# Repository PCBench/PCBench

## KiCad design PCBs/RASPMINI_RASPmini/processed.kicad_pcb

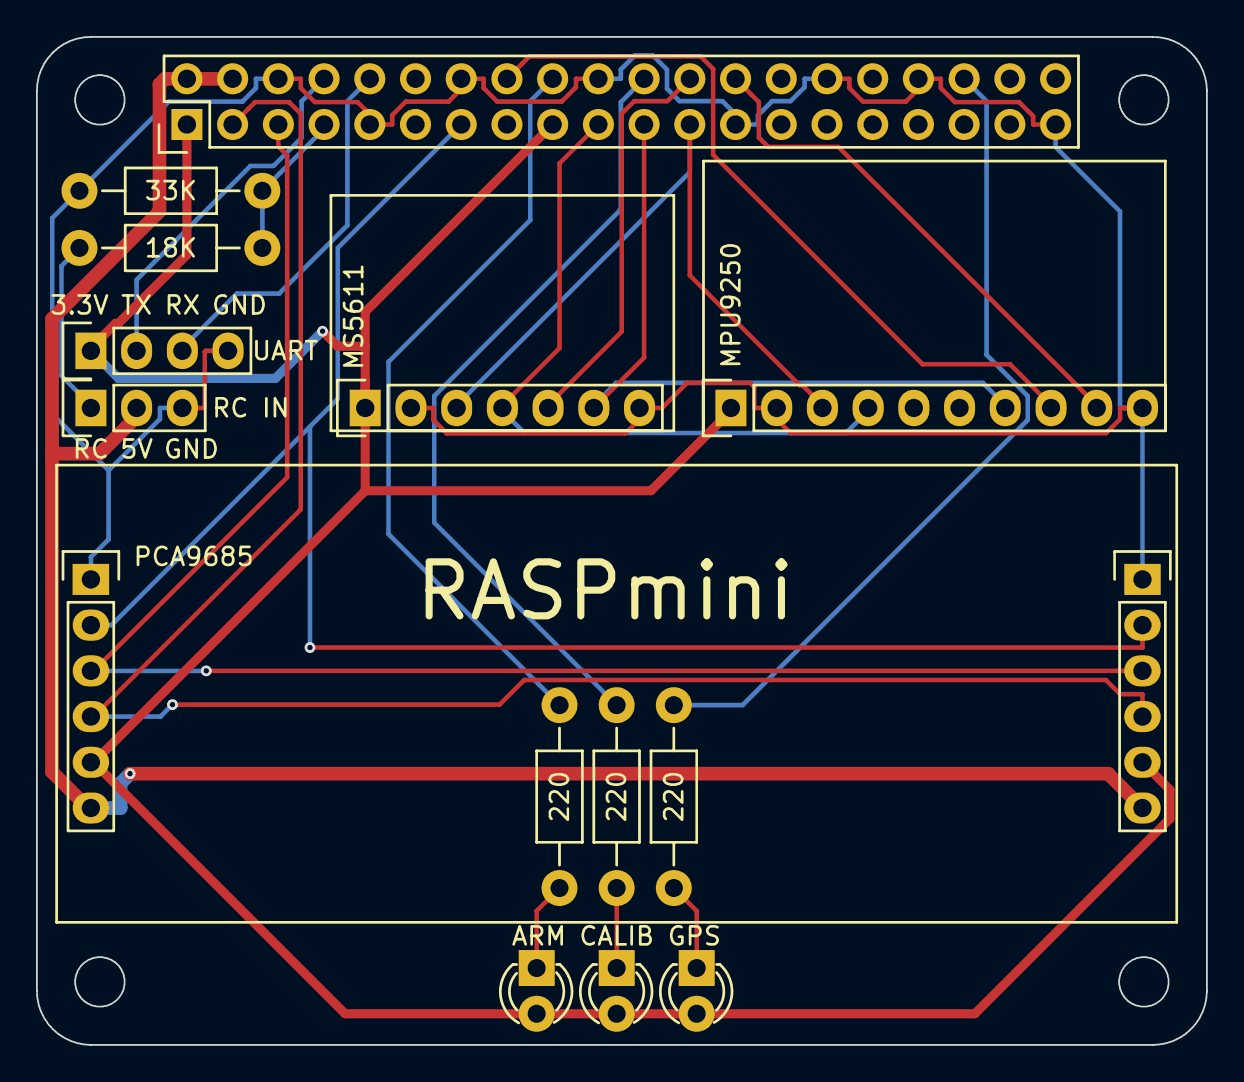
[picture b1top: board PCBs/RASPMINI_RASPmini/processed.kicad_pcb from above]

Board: 2 copper layers, 65.0 x 56.0 mm, 14 parts (0 on the bottom side), 22 nets.

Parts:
D1: ARM; LED-3MM
D2: CALIB; LED-3MM
D3: GPS; LED-3MM
P0: Raspberry PI GPIO; Pin_Header_Straight_2x20
P1: MPU9250
P2: MS5611
P3: PCA9685
P5: UART; Pin_Header_Straight_1x04
P6: RC IN; Pin_Header_Straight_1x03
R1: 18K; Resistor_Horizontal_RM10mm
R2: 33K; Resistor_Horizontal_RM10mm
R3, R4, R5: 220; Resistor_Horizontal_RM10mm

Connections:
+3V3: D1.2, D2.2, D3.2, P0.1, P0.17, P1.1, P2.1, P3.5, P5.1
+5V: P0.2, P0.4, P3.6, P6.2
/CS_BARO: P0.24, P2.5
/CS_MPU: P0.26, P1.9
/EN_PWM: P0.13, P3.2
/LED_ARM: P0.18, R3.2
/LED_CALIBRATION: P0.22, R4.2
/LED_GPS: P0.36, R5.2
/MISO: P0.21, P1.7, P2.6
/MOSI: P0.19, P1.4, P2.4
/MPU_DRDY: P0.16, P1.8
/RC_INPUT: P0.7, R1.2, R2.1
/RXD: P0.10, P5.3
/SCL: P0.5, P3.3
/SCLK: P0.23, P1.3, P2.3
/SDA: P0.3, P3.4
/TXD: P0.8, P5.2
GND: P0.6, P0.9, P0.14, P0.20, P0.25, P0.30, P0.34, P0.39, P1.2, P1.10, P2.2, P2.7, P3.1, P5.4, P6.3, R2.2
unnamed: D1.1, R3.1
unnamed: D2.1, R4.1
unnamed: D3.1, R5.1
unnamed: P6.1, R1.1

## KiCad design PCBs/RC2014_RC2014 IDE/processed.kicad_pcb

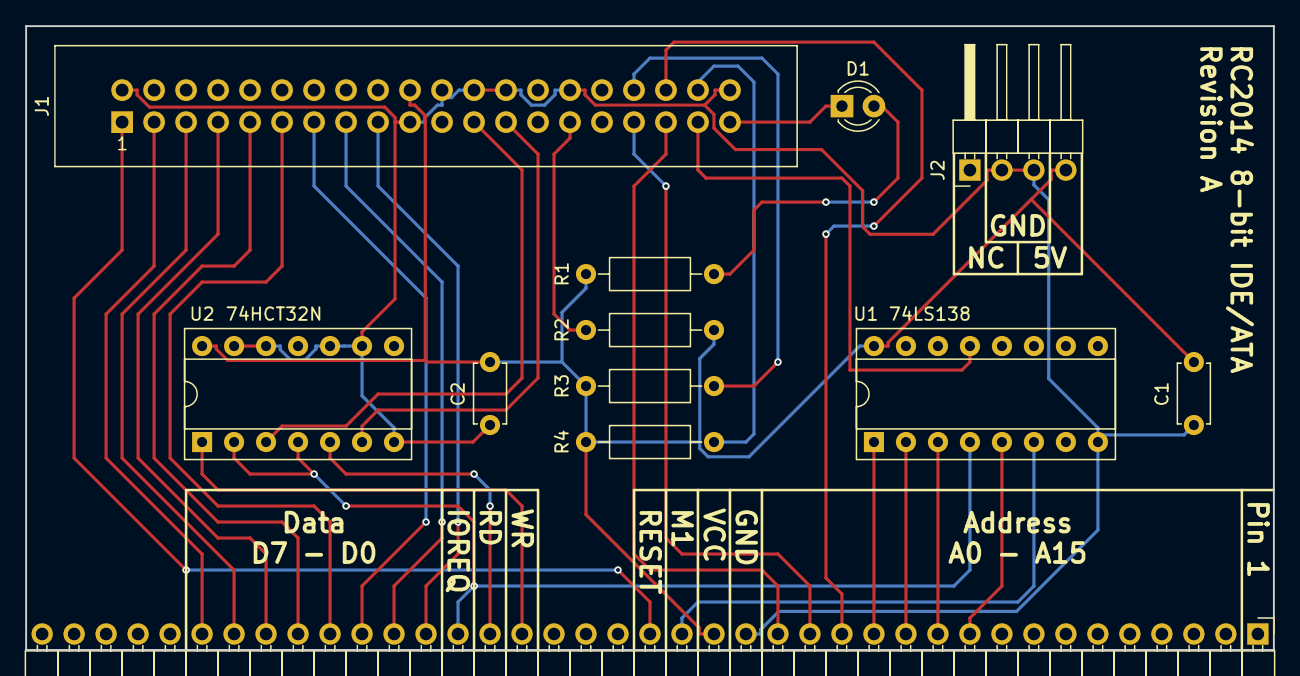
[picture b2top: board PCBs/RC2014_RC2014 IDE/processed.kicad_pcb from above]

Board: 2 copper layers, 99.1 x 49.5 mm, 12 parts (0 on the bottom side), 30 nets.

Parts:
C1, C2: 100nF; C_Disc_D4.7mm_W2.5mm_P5.00mm
D1: LED; LED_D3.0mm
J1: CONN_02X20; IDC_Header_Straight_40pins
J2: Device power; Pin_Header_Angled_1x04_Pitch2.54mm
J4: CONN_01X39; Pin_Header_Angled_1x39_Pitch2.54mm
R1: 330; R_Axial_DIN0207_L6.3mm_D2.5mm_P10.16mm_Horizontal
R2, R3, R4: 1k; R_Axial_DIN0207_L6.3mm_D2.5mm_P10.16mm_Horizontal
U1: 74LS138; DIP-16_W7.62mm_Socket
U2: 74HCT32N; DIP-14_W7.62mm_Socket

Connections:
/IORD: J1.25, U2.6
/IOWR: J1.23, U2.3
A0: J1.35, J4.16
A1: J1.33, J4.15
A2: J1.36, J4.14
A3: J4.13, U1.1
A4: J4.12, U1.2
A5: J4.11, U1.3
A6: J4.10, U1.5
BUSY: D1.1, J1.39
D0: J1.17, J4.27
D1: J1.15, J4.28
D2: J1.13, J4.29
D3: J1.11, J4.30
D4: J1.9, J4.31
D5: J1.7, J4.32
D6: J1.5, J4.33
D7: J1.3, J4.34
GND: C1.2, C2.2, J1.2, J1.19, J1.22, J1.24, J1.26, J1.30, J1.40, J2.2, J2.3, J4.17, U1.8, U2.7, U2.9, U2.10, U2.12, U2.13
IOREQ: J4.26, U1.4, U2.2, U2.4
M1: J4.19, U1.6
unnamed: D1.2, R1.1
unnamed: J1.29, R2.1
unnamed: J1.34, R3.2
unnamed: J1.38, R4.2
PORT16: J1.37, U1.13
RD: J4.25, U2.5
RESET: J1.1, J4.20
VCC: C1.1, C2.1, J1.20, J2.4, J4.18, R1.2, R2.2, R3.1, R4.1, U1.16, U2.14
WR: J4.24, U2.1

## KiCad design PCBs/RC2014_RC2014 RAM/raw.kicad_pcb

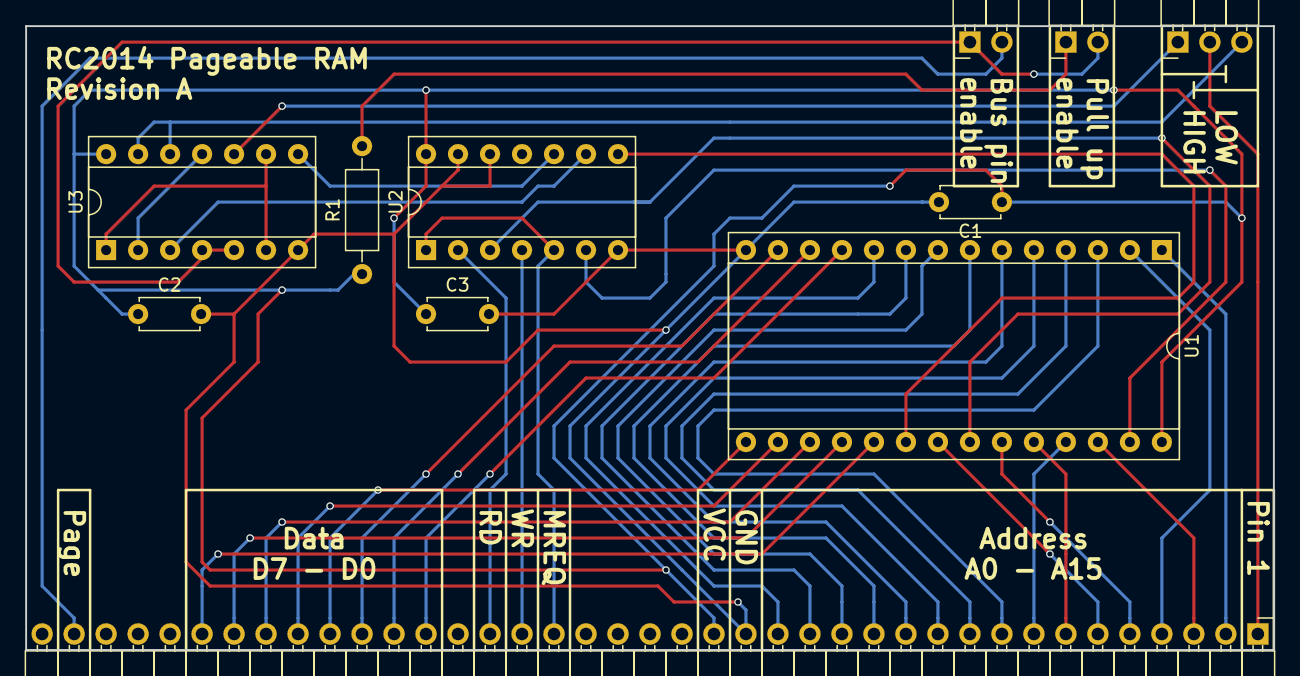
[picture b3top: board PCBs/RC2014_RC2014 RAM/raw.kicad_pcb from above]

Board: 2 copper layers, 99.1 x 49.5 mm, 11 parts (0 on the bottom side), 41 nets.

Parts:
C1, C2, C3: 100nF; C_Disc_D4.7mm_W2.5mm_P5.00mm
J1: Page PullUp; Pin_Header_Angled_1x02_Pitch2.54mm
J2: HIGH | LOW; Pin_Header_Angled_1x03_Pitch2.54mm
J3: Bus enable; Pin_Header_Angled_1x02_Pitch2.54mm
J4: CONN_01X39; Pin_Header_Angled_1x39_Pitch2.54mm
R1: 10k; R_Axial_DIN0207_L6.3mm_D2.5mm_P10.16mm_Horizontal
U1: HM62256BLP-7; DIP-28_W15.24mm_Socket
U2: 74LS32; DIP-14_W7.62mm_Socket
U3: 74HCT00; DIP-14_W7.62mm_Socket

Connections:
A0: J4.16, U1.10
A1: J4.15, U1.9
A2: J4.14, U1.8
A3: J4.13, U1.7
A4: J4.12, U1.6
A5: J4.11, U1.5
A6: J4.10, U1.4
A7: J4.9, U1.3
A8: J4.8, U1.25
A9: J4.7, U1.24
A10: J4.6, U1.21
A11: J4.5, U1.23
A12: J4.4, U1.2
A13: J4.3, U1.26
A14: J4.2, U1.1
A15: J2.2, J4.1
CS: U1.20, U2.8
D0: J4.27, U1.11
D1: J4.28, U1.12
D2: J4.29, U1.13
D3: J4.30, U1.15
D4: J4.31, U1.16
D5: J4.32, U1.17
D6: J4.33, U1.18
D7: J4.34, U1.19
EN: U3.1, U3.6, U3.9
GND: C1.2, C2.2, C3.2, J4.17, U1.14, U2.7, U2.12, U2.13, U3.7
HIGH: J2.1, U3.10
LOW: J2.3, U3.12, U3.13
MREQ: J4.23, U2.1, U2.5
unnamed: J1.1, R1.2
unnamed: J3.2, J4.38
unnamed: U1.22, U2.3
unnamed: U1.27, U2.6
unnamed: U2.9, U3.3
unnamed: U2.10, U3.8
unnamed: U3.2, U3.11
PAGE: J1.2, J3.1, U3.4, U3.5
RD: J4.25, U2.2
VCC: C1.1, C2.1, C3.1, J4.18, R1.1, U1.28, U2.14, U3.14
WR: J4.24, U2.4

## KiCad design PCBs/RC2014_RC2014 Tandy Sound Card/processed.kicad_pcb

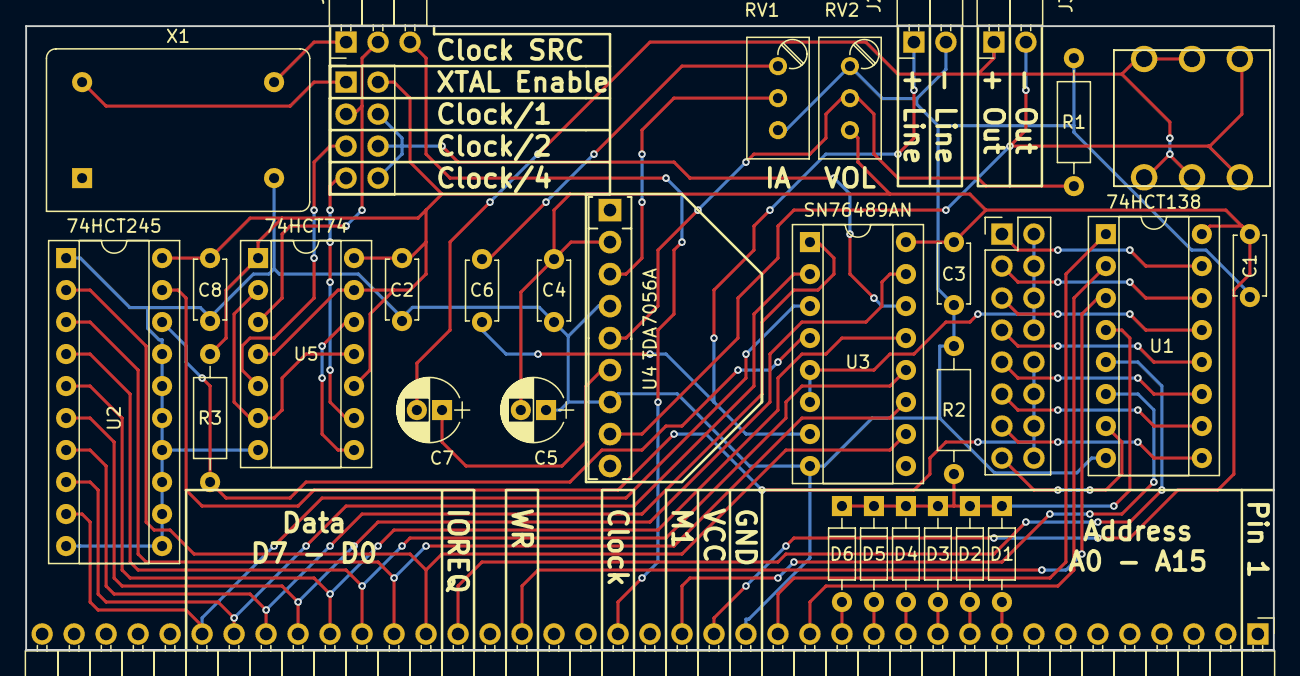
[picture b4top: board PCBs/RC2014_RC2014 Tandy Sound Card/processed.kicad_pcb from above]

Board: 2 copper layers, 99.1 x 49.5 mm, 32 parts (0 on the bottom side), 49 nets.

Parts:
C1, C2, C3, C4, C8: 100nF; C_Disc_D4.7mm_W2.5mm_P5.00mm
C5: 220uF; CP_Radial_D5.0mm_P2.00mm
C6: 470nF; C_Disc_D4.7mm_W2.5mm_P5.00mm
C7: 470uF; CP_Radial_D5.0mm_P2.00mm
D1, D2, D3, D4, D5, D6: 1N4848; D_DO-35_SOD27_P7.62mm_Horizontal
J1: CONN_01X39; Pin_Header_Angled_1x39_Pitch2.54mm
J2: Line Out; Pin_Header_Angled_1x02_Pitch2.54mm
J3: Speaker Out; Pin_Header_Angled_1x02_Pitch2.54mm
J4: CONN_02X08; Pin_Header_Straight_2x08_Pitch2.54mm
J5: JACK_TRS_6PINS; cliff_fcr1295_socket
J6: CONN_02X04; Pin_Header_Straight_2x04_Pitch2.54mm
JP1: Clock source; Pin_Header_Angled_1x03_Pitch2.54mm
R1: 1k; R_Axial_DIN0207_L6.3mm_D2.5mm_P10.16mm_Horizontal
R2, R3: 10k; R_Axial_DIN0207_L6.3mm_D2.5mm_P10.16mm_Horizontal
RV1, RV2: 10k; Potentiometer_Trimmer_Bourns_3296W
U1: 74HCT138; DIP-16_W7.62mm_Socket
U2: 74HCT245; DIP-20_W7.62mm_Socket
U3: SN76489AN; DIP-16_W7.62mm_Socket
U4: TDA7056A; SIP9_Housing
U5: 74HCT74; DIP-14_W7.62mm_Socket
X1: 1MHz; Oscillator_DIP-14

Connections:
/RD_Port_0: J4.9, U1.11
/RD_Port_1: J4.11, U1.10
/RD_Port_2: J4.13, U1.9
/RD_Port_3: J4.15, U1.7
/WR_Port_0: J4.1, U1.15
/WR_Port_1: J4.3, U1.14
/WR_Port_2: J4.5, U1.13
/WR_Port_3: J4.7, U1.12
A0: J1.16, U1.1
A1: J1.15, U1.2
A2: D6.2, J1.14
A3: D5.2, J1.13
A4: D4.2, J1.12
A5: D3.2, J1.11
A6: D2.2, J1.10
A7: D1.2, J1.9
CLOCK: J1.21, JP1.3
CLOCK/1: J6.3, JP1.2, U5.3
CLOCK/2: J6.5, U5.5
CLOCK/4: J6.7, U5.9
D0: J1.27, U2.2, U3.10
D1: J1.28, U2.3, U3.11
D2: J1.29, U2.4, U3.12
D3: J1.30, U2.5, U3.13
D4: J1.31, U2.6, U3.15
D5: J1.32, U2.7, U3.1
D6: J1.33, U2.8, U3.2
D7: J1.34, U2.9, U3.3
GND: C1.2, C2.2, C3.2, C4.1, C5.1, C8.2, J1.17, J2.2, R1.2, R2.2, RV1.3, RV2.1, U1.8, U2.1, U2.10, U2.11, U2.12, U2.13, U2.14, U2.15, U2.16, U2.17, U3.8, U4.4, U4.7, U5.7, X1.7
IOREQ: J1.26, U1.5
IO_RD: J4.10, J4.12, J4.14, J4.16, U2.19
IO_WR: J4.2, J4.4, J4.6, J4.8, U3.5, U3.6
M1: J1.19, U1.6
unnamed: C6.2, RV1.1
unnamed: C7.2, J3.1, J5.2, J5.3, J5.5, J5.6
unnamed: D1.1, D2.1, D3.1, D4.1, D5.1, D6.1, R2.1, U1.4
unnamed: J6.1, X1.14
unnamed: JP1.1, X1.8
unnamed: R1.1, RV2.2, U4.5
unnamed: R3.2, U2.18, U3.4
unnamed: RV1.2, U4.3
unnamed: U5.2, U5.6, U5.11
unnamed: U5.8, U5.12
SND_CLOCK: J6.4, J6.6, J6.8, U3.14
SND_OUT: C6.1, J2.1, U3.7
SPKR_OUT+: C7.1, U4.6
SPKR_OUT-: J3.2, J5.1, J5.4, U4.8
VCC: C1.1, C2.1, C3.1, C4.2, C5.2, C8.1, J1.18, J6.2, R3.1, RV2.3, U1.16, U2.20, U3.16, U4.2, U5.1, U5.4, U5.10, U5.13, U5.14
WR: J1.24, U1.3

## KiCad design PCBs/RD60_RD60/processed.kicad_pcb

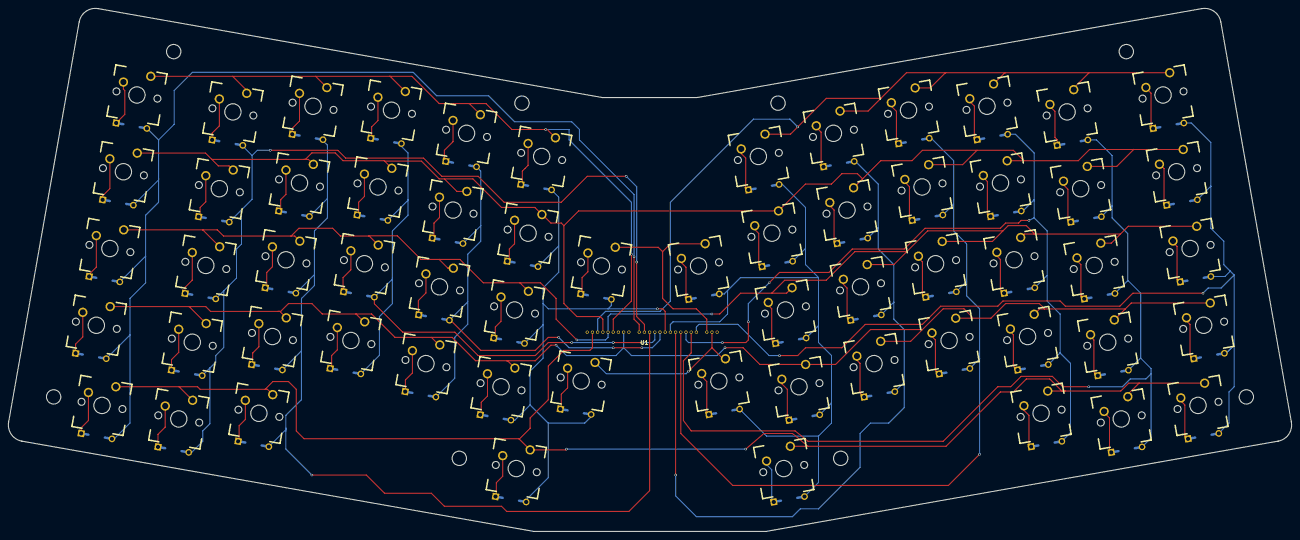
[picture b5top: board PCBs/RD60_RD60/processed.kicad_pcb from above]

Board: 2 copper layers, 313.6 x 127.8 mm, 61 parts (0 on the bottom side), 80 nets.

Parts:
U1: k270
U2, U3, U4, U5, U6, U7, U8, U9, U10, U11, U12, U13, U14, U15, U16, U17, U18, U19, U20, U21, U22, U23, U24, U25, U26, U27, U28, U29, U30, U31, U32, U33, U34, U35, U36, U37, U38, U39, U40, U41, U42, U43, U44, U45, U46, U47, U48, U49, U50, U51, U52, U53, U54, U55, U56, U57, U58, U59, U60, U61: mx1a

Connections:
2: U1.2, U6.1, U11.1, U16.1, U29.1, U34.1, U51.1, U56.1, U61.1
3: U1.3, U35.1, U39.1, U43.1, U47.1, U52.1, U57.1
4: U1.4, U3.1, U8.1, U13.1, U18.1, U22.1, U26.1, U36.1, U40.1, U44.1, U48.1, U53.1, U58.1
5: U1.5, U4.1, U9.1, U14.1, U19.1, U23.1, U27.1, U37.1, U41.1, U45.1, U49.1, U54.1, U59.1
6: U1.6, U2.1, U7.1, U12.1, U17.1, U21.1, U25.1
8: U1.8, U5.1, U10.1, U15.1, U20.1, U24.1, U28.1, U38.1, U42.1, U46.1, U50.1, U55.1, U60.1
10: U1.10, U2.2, U3.2, U4.2, U5.2, U6.2
11: U1.11, U7.2, U8.2, U9.2, U10.2, U11.2
12: U1.12, U12.2, U13.2, U14.2, U15.2, U16.2
13: U1.13, U17.2, U18.2, U19.2, U20.2
14: U1.14, U21.2, U22.2, U23.2, U24.2
15: U1.15, U25.2, U26.2, U27.2, U28.2, U29.2, U30.2, U31.2
16: U1.16, U32.2, U33.2, U34.2, U35.2, U36.2, U37.2, U38.2
17: U1.17, U39.2, U40.2, U41.2, U42.2
18: U1.18, U43.2, U44.2, U45.2, U46.2
19: U1.19, U47.2, U48.2, U49.2, U50.2, U51.2
20: U1.20, U52.2, U53.2, U54.2, U55.2, U56.2
21: U1.21, U57.2, U58.2, U59.2, U60.2, U61.2
22: U1.22, U30.1, U32.1
23: U1.23, U31.1, U33.1
unnamed: U2.3, U2.4
unnamed: U3.3, U3.4
unnamed: U4.3, U4.4
unnamed: U5.3, U5.4
unnamed: U6.3, U6.4
unnamed: U7.3, U7.4
unnamed: U8.3, U8.4
unnamed: U9.3, U9.4
unnamed: U10.3, U10.4
unnamed: U11.3, U11.4
unnamed: U12.3, U12.4
unnamed: U13.3, U13.4
unnamed: U14.3, U14.4
unnamed: U15.3, U15.4
unnamed: U16.3, U16.4
unnamed: U17.3, U17.4
unnamed: U18.3, U18.4
unnamed: U19.3, U19.4
unnamed: U20.3, U20.4
unnamed: U21.3, U21.4
unnamed: U22.3, U22.4
unnamed: U23.3, U23.4
unnamed: U24.3, U24.4
unnamed: U25.3, U25.4
unnamed: U26.3, U26.4
unnamed: U27.3, U27.4
unnamed: U28.3, U28.4
unnamed: U29.3, U29.4
unnamed: U30.3, U30.4
unnamed: U31.3, U31.4
unnamed: U32.3, U32.4
unnamed: U33.3, U33.4
unnamed: U34.3, U34.4
unnamed: U35.3, U35.4
unnamed: U36.3, U36.4
unnamed: U37.3, U37.4
unnamed: U38.3, U38.4
unnamed: U39.3, U39.4
unnamed: U40.3, U40.4
unnamed: U41.3, U41.4
unnamed: U42.3, U42.4
unnamed: U43.3, U43.4
unnamed: U44.3, U44.4
unnamed: U45.3, U45.4
unnamed: U46.3, U46.4
unnamed: U47.3, U47.4
unnamed: U48.3, U48.4
unnamed: U49.3, U49.4
unnamed: U50.3, U50.4
unnamed: U51.3, U51.4
unnamed: U52.3, U52.4
unnamed: U53.3, U53.4
unnamed: U54.3, U54.4
unnamed: U55.3, U55.4
unnamed: U56.3, U56.4
unnamed: U57.3, U57.4
unnamed: U58.3, U58.4
unnamed: U59.3, U59.4
unnamed: U60.3, U60.4
unnamed: U61.3, U61.4

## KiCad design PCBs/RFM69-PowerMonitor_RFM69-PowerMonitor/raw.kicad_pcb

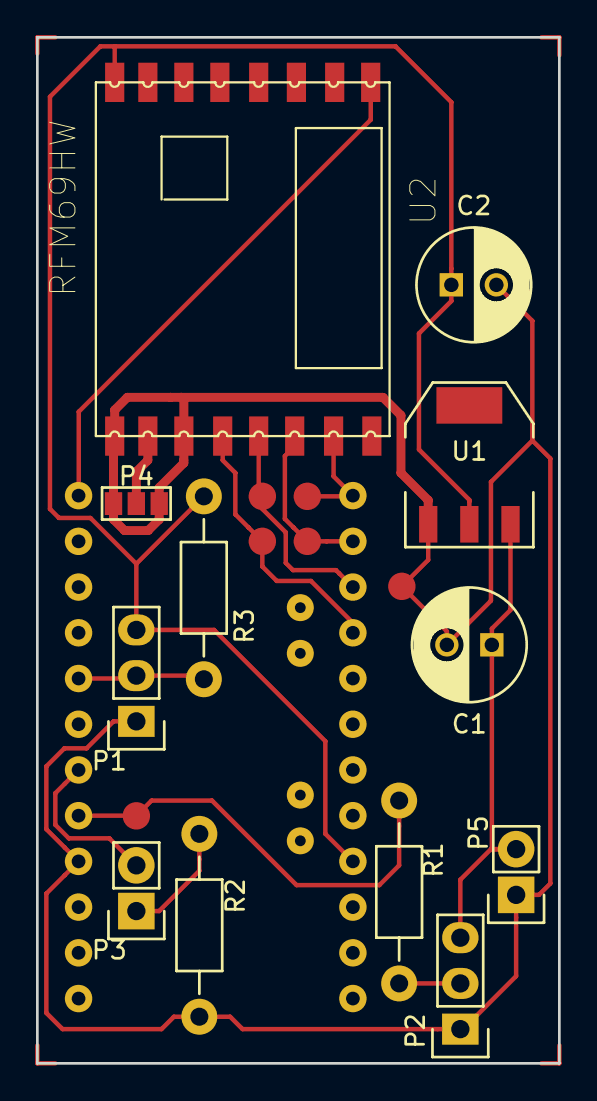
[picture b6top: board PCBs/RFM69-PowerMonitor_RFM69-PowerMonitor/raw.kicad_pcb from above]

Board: 2 copper layers, 29.0 x 57.0 mm, 13 parts (1 on the bottom side), 14 nets.

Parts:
C1: 10uF; C_Radial_D6.3_L11.2_P2.5
C2: 100uF; C_Radial_D6.3_L11.2_P2.5
P1: 1WIRE; Pin_Header_Straight_1x03
P2: CONN_PIR; Pin_Header_Straight_1x03
P3: MTR; Pin_Header_Straight_1x02
P4: ANT; GS3
P5: CONN_PWR; Pin_Header_Straight_1x02
R1, R2: 470; Resistor_Horizontal_RM10mm
R3: 2.2k; Resistor_Horizontal_RM10mm
U1: AP1117D33; SOT-223
U2: RFM69HW; RFM
uP1: ARDUPROMINI-6; ArduProMini-6

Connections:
+5V: C1.1, P2.3, P5.2, U1.3
GND: C1.2, C2.2, P1.1, P2.1, P4.1, P4.3, P5.1, R2.1, U1.1, U2.GNDA, U2.GNDB, uP1.10
unnamed: C2.1, P1.3, R3.1, U1.2, U2.VCC, uP1.22
unnamed: P1.2, R3.2, uP1.14
unnamed: P2.2, R1.2
unnamed: P3.1, R2.2
unnamed: P3.2, uP1.12
unnamed: P4.2, U2.ANT
unnamed: R1.1, uP1.11
unnamed: U2.MISO, uP1.28
unnamed: U2.MOSI, uP1.29
unnamed: U2.NSS, uP1.30
unnamed: U2.RESE, uP1.18
unnamed: U2.SCK, uP1.27
